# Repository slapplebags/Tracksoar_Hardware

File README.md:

View this project on [CADLAB.io](https://cadlab.io/project/1187). 

# Tracksoar_Hardware

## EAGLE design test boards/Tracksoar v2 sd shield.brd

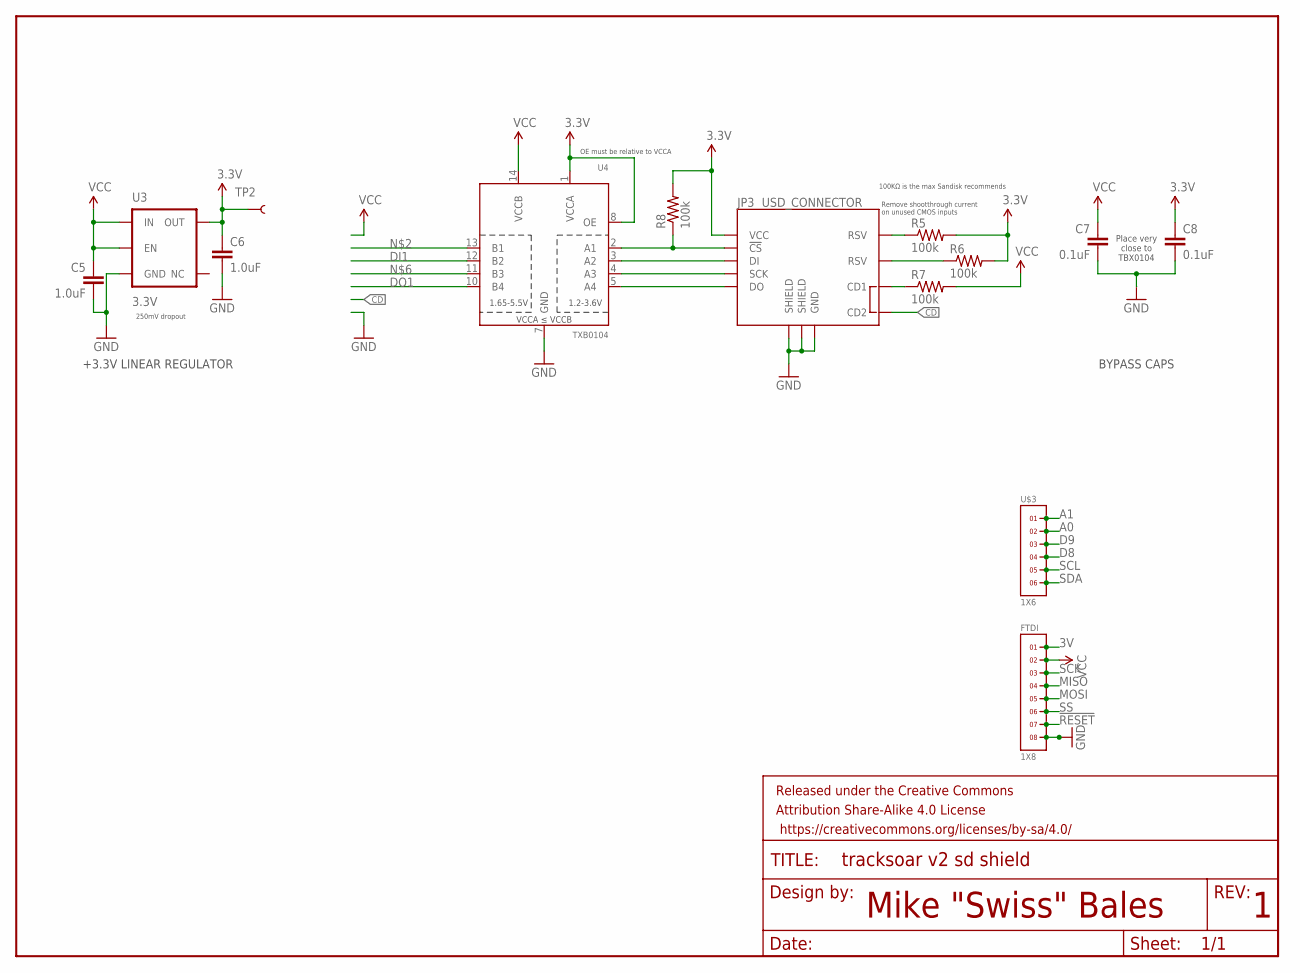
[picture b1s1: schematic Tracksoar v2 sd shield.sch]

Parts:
C5, C6: 1.0uF; 0603-CAP
C7, C8: 0.1uF; 0603-CAP
FRAME1: FRAME-LETTER; CREATIVE_COMMONS
FTDI: 1X8
JP3: USD_CONNECTOR; MICRO-SD-SOCKET-PP
R5, R6, R7, R8: 100k; 0603-RES
TP2: TEST-POINT3; PAD.03X.03
U3: 3.3V; SOT23-5
U4: TXB0104; SO14
U$3: 1X6

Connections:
3V: FTDI.1
3V3: C6.1, C8.1, JP3.VCC, R5.2, R6.2, R8.2, TP2.P$1, U3.5 (OUT), U4.1 (VCCA), U4.8 (OE)
!CS_3V1: JP3.CS (!CS), R8.1, U4.2 (A1)
!RESET: FTDI.7
A0: U$3.2
A1: U$3.1
CD: JP3.CD2
CDSDSD1: JP3.CD1, R7.1
D8: U$3.4
D9: U$3.3
DI1: U4.12 (B2)
DI_3V1: JP3.DI, U4.3 (A2)
DO1: U4.10 (B4)
DO_3V1: JP3.DO, U4.5 (A4)
GND: C5.2, C6.2, C7.2, C8.2, FTDI.8, JP3.GND, JP3.GND1 (SHIELD), JP3.GND3 (SHIELD), U3.2 (GND), U4.7 (GND)
MISO: FTDI.4
MOSI: FTDI.5
RSV@3: JP3.RSV1 (RSV), R5.1
RSV@4: JP3.RSV2 (RSV), R6.1
SCK: FTDI.3
SCK_3V1: JP3.SCLK (SCK), U4.4 (A3)
SCL: U$3.5
SDA: U$3.6
SS: FTDI.6
VCC: FTDI.2
VDD_IO: C5.1, C7.1, R7.2, U3.1 (IN), U3.3 (EN), U4.14 (VCCB)

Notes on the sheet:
Mike "Swiss" Bales
Remove shootthrough current on unused CMOS inputs
Place very close to TBX0104
OE must be relative to VCCA
+3.3V LINEAR REGULATOR
BYPASS CAPS
100KΩ is the max Sandisk recommends
250mV dropout

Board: 4 copper layers, 15 parts (13 on the bottom side), 10 nets, no tracks yet.

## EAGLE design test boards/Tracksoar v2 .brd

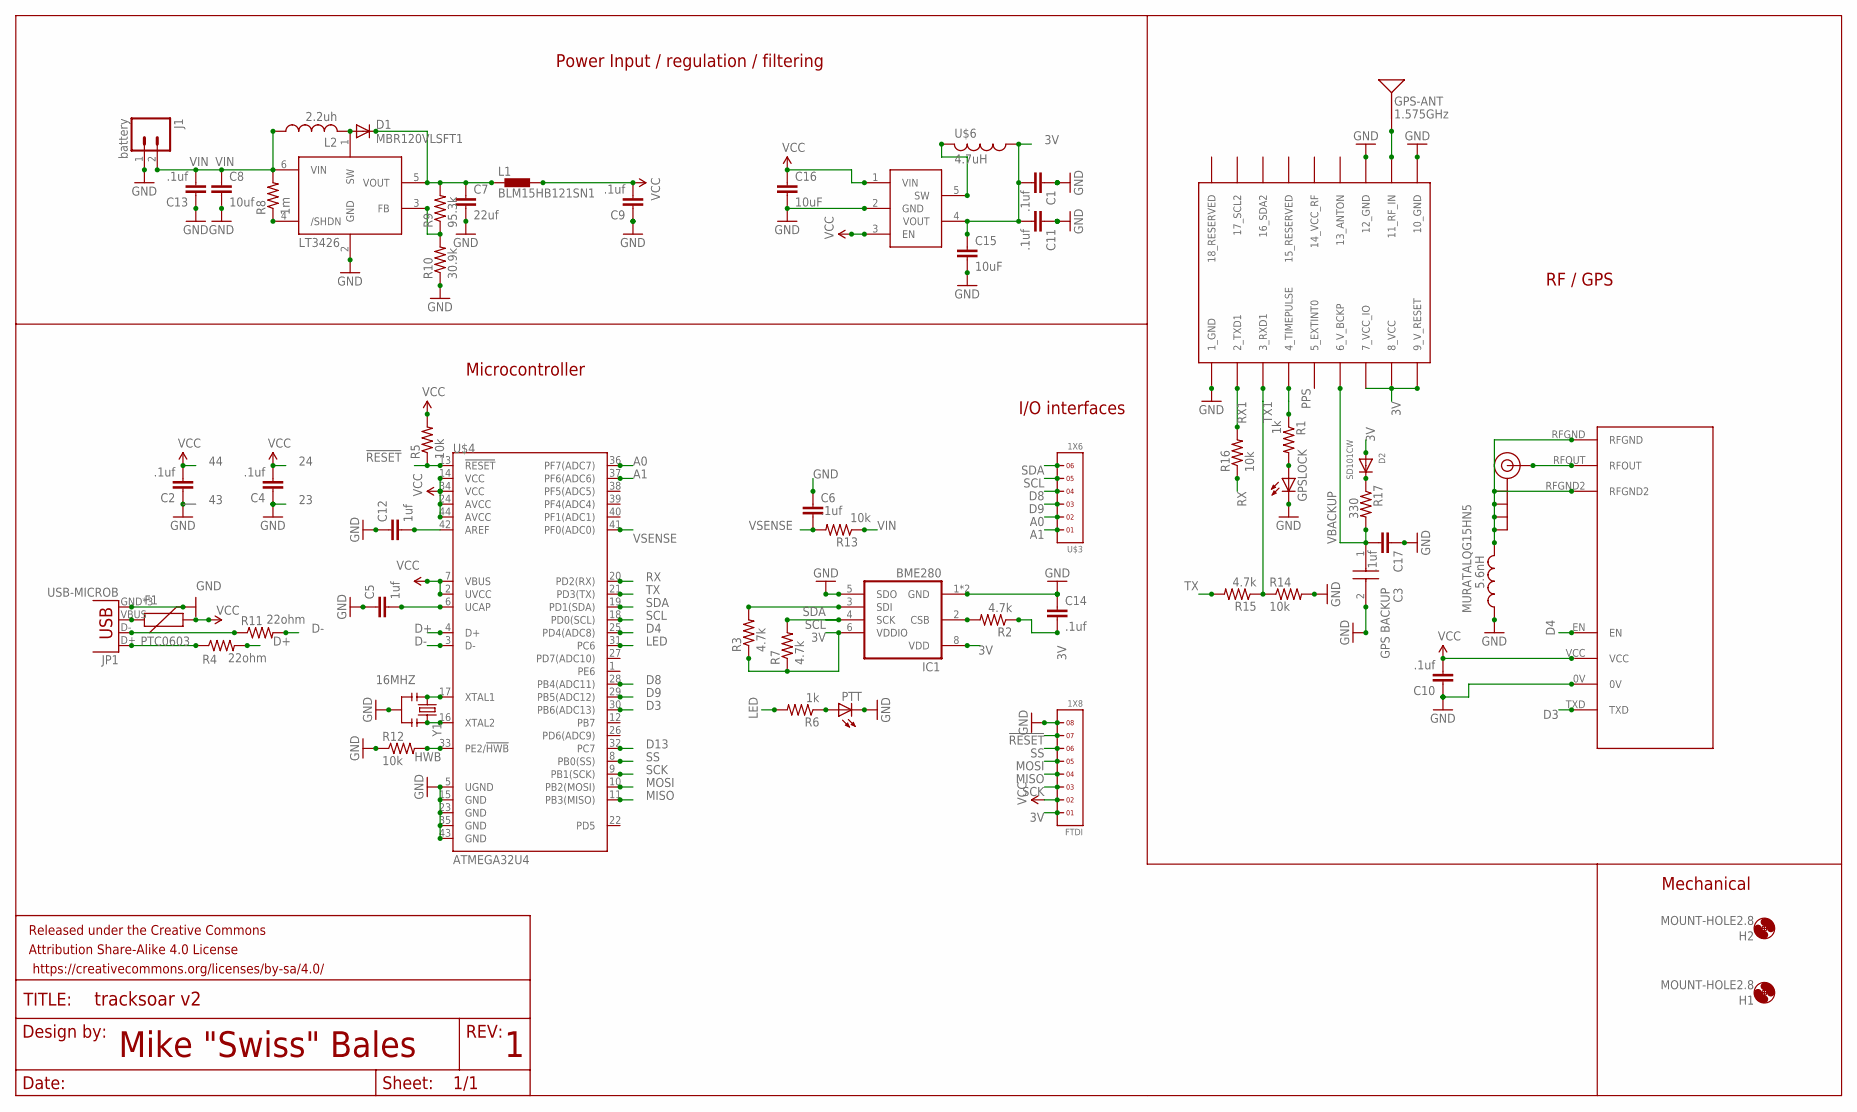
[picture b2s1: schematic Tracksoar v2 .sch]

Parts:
C1, C2, C4, C6, C9, C10, C11, C13, C14, C17: .1uf; 0402-CAP
C3: GPS BACKUP; DSK-3R3H204T614-H2L
C5, C12: 1uf; 0402-CAP
C7: 22uf; 0805
C8: 10uf; 0805
C15, C16: 10uF; 0603
D1: MBR120VLSFT1; SOD123
D2: SD101CW; SOD-123
F1: PTC0603; 0603
FRAME1: FRAME-LETTER; CREATIVE_COMMONS
FTDI: 1X8
GPS-ANT: 1.575GHz; ANT-GPS-2X7MM
GPSLOCK: LEDCHIP-LED0603; CHIP-LED0603
H1, H2: MOUNT-HOLE2.8; 2,8
IC1: BME280
J1: battery; JST-2-PTH
J$1: SMA_EDGE; SMA-EDGE
JP1: USB-MICROB
L1: BLM15HB121SN1; 0402
L2: 2.2uh; L1812
LT3426: LT3426; SOT23-6
MURATALQG15HN5: 5.6nH; RESC0402_N
PTT: LEDCHIP-LED0603; CHIP-LED0603
R1, R6: 1k; R0402
R2, R3, R7, R15: 4.7k; R0402
R4, R11: 22ohm; R0402
R5, R12, R13, R14, R16: 10k; R0402
R8: 1m; R0402
R9: 95.3k; R0402
R10: 30.9k; R0402
R17: 330; R0402
U$1: UBLOX_MAX
U$2: RADIOMETRIX-HX1
U$3: 1X6
U$4: ATMEGA32U4; QFN-44-NOPAD
U$5: PAM2305; DBV_R-PDSO-G5
U$6: 4.7uH; RESC0805_N
Y1: 16MHZ; RESONATOR-SMD

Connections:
3V: C1.2, C11.2, C14.2, C15.1, D2.A, FTDI.1, IC1.6 (VDDIO), IC1.8 (VDD), R2.1, R3.1, R7.1, U$1.7_VCC_IO, U$1.8_VCC, U$1.9_V_RESET, U$5.4 (VOUT), U$6.1
!RESET: FTDI.7, R5.1, U$4.13 (!RESET)
A0: U$3.2, U$4.36 (PF7(ADC7))
A1: U$3.1, U$4.37 (PF6(ADC6))
D3: U$2.TXD, U$4.30 (PB6(ADC13))
D4: U$2.EN, U$4.25 (PD4(ADC8))
D8: U$3.4, U$4.28 (PB4(ADC11))
D9: U$3.3, U$4.29 (PB5(ADC12))
D13: U$4.32 (PC7)
D+: R4.2, U$4.4 (D+)
D-: R11.2, U$4.3 (D-)
GND: C1.1, C2.1, C3.2 (-), C4.1, C5.1, C6.1, C7.2, C8.2, C9.1, C10.1, C11.1, C12.1, C13.1, C14.1, C15.2, C16.2, C17.1, FTDI.8, GPSLOCK.C, IC1.1 (GND), IC1.5 (SDO), IC1.7 (GND), J1.1, JP1.GND, JP1.MT1 (GND), JP1.MT2 (GND), LT3426.2 (GND), MURATALQG15HN5.1, PTT.C, R10.1, R12.1, R14.2, U$1.1_GND, U$1.10_GND, U$1.12_GND, U$2.0V, U$4.5 (UGND), U$4.15 (GND), U$4.23 (GND), U$4.35 (GND), U$4.43 (GND), U$5.2 (GND), Y1.2
HWB: R12.2, U$4.33 (PE2/!HWB)
LED: R6.2, U$4.31 (PC6)
MISO: FTDI.4, U$4.11 (PB3(MISO))
MOSI: FTDI.5, U$4.10 (PB2(MOSI))
unnamed: J$1.SIG (SIGNAL), U$2.RFOUT
unnamed: IC1.2 (CSB), R2.2
unnamed: GPSLOCK.A, R1.2
unnamed: GPS-ANT.1, U$1.11_RF_IN
unnamed: JP1.D-, R11.1
unnamed: JP1.D+, R4.1
unnamed: D1.A, L2.2, LT3426.1 (SW)
unnamed: LT3426.4 (/SHDN), R8.1
unnamed: LT3426.3 (FB), R9.1, R10.2
unnamed: F1.1, JP1.VBUS
unnamed: C12.2, U$4.42 (AREF)
unnamed: C7.1, D1.C, L1.1, LT3426.5 (VOUT), R9.2
unnamed: C5.2, U$4.6 (UCAP)
unnamed: U$5.5 (SW), U$6.2
unnamed: D2.C, R17.1
unnamed: PTT.A, R6.1
PPS: R1.1, U$1.4_TIMEPULSE
RFGND: J$1.GND@0 (GND), J$1.GND@1 (GND), J$1.GND@2 (GND), J$1.GND@3 (GND), MURATALQG15HN5.2, U$2.RFGND, U$2.RFGND2
RX: R16.1, U$4.20 (PD2(RX))
RX1: R16.2, U$1.2_TXD1
SCK: FTDI.3, U$4.9 (PB1(SCK))
SCL: IC1.4 (SCK), R7.2, U$3.5, U$4.18 (PD0(SCL))
SDA: IC1.3 (SDI), R3.2, U$3.6, U$4.19 (PD1(SDA))
SS: FTDI.6, U$4.8 (PB0(SS))
TX: R15.2, U$4.21 (PD3(TX))
TX1: R14.1, R15.1, U$1.3_RXD1
VBACKUP: C3.1 (+), C17.2, R17.2, U$1.6_V_BCKP
VCC: C2.2, C4.2, C9.2, C10.2, C16.1, F1.2, FTDI.2, L1.2, R5.2, U$2.VCC, U$4.2 (UVCC), U$4.7 (VBUS), U$4.14 (VCC), U$4.24 (AVCC), U$4.34 (VCC), U$4.44 (AVCC), U$5.1 (VIN), U$5.3 (EN)
VIN: C8.1, C13.2, J1.2, L2.1, LT3426.6 (VIN), R8.2, R13.1
VSENSE: C6.2, R13.2, U$4.41 (PF0(ADC0))
XTAL1: U$4.17 (XTAL1), Y1.1
XTAL2: U$4.16 (XTAL2), Y1.3

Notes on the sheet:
Mike "Swiss" Bales
Power Input / regulation / filtering
RF / GPS
Microcontroller
I/O interfaces
Mechanical

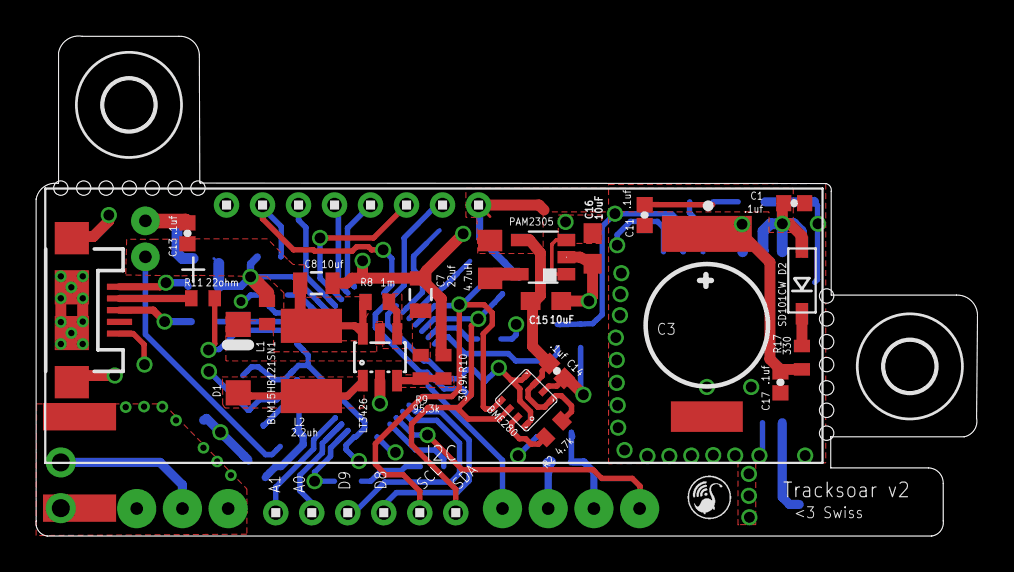
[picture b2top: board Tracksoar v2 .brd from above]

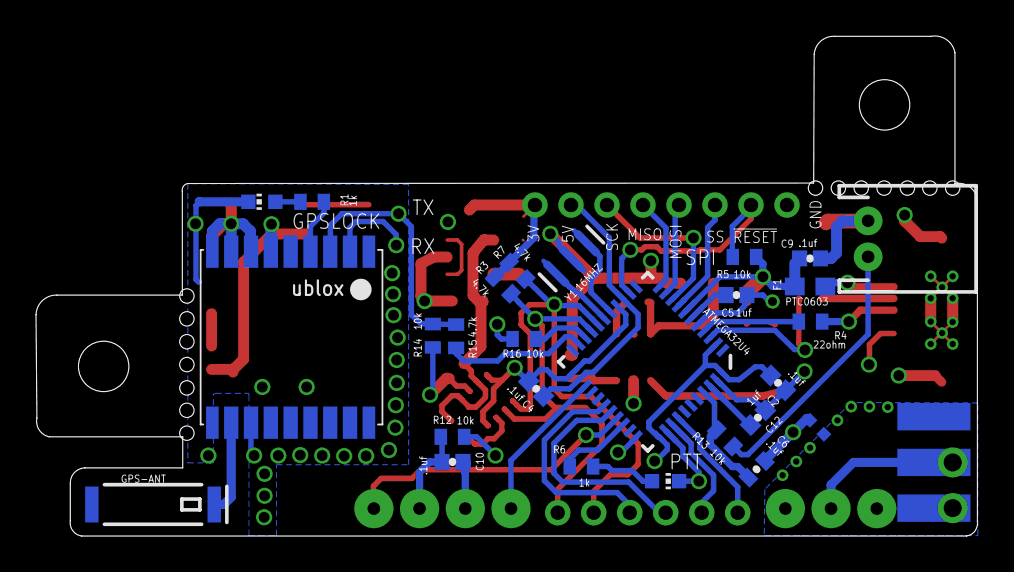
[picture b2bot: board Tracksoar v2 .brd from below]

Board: 4 copper layers, 52.3 x 27.8 mm, 59 parts (28 on the bottom side), 47 nets.

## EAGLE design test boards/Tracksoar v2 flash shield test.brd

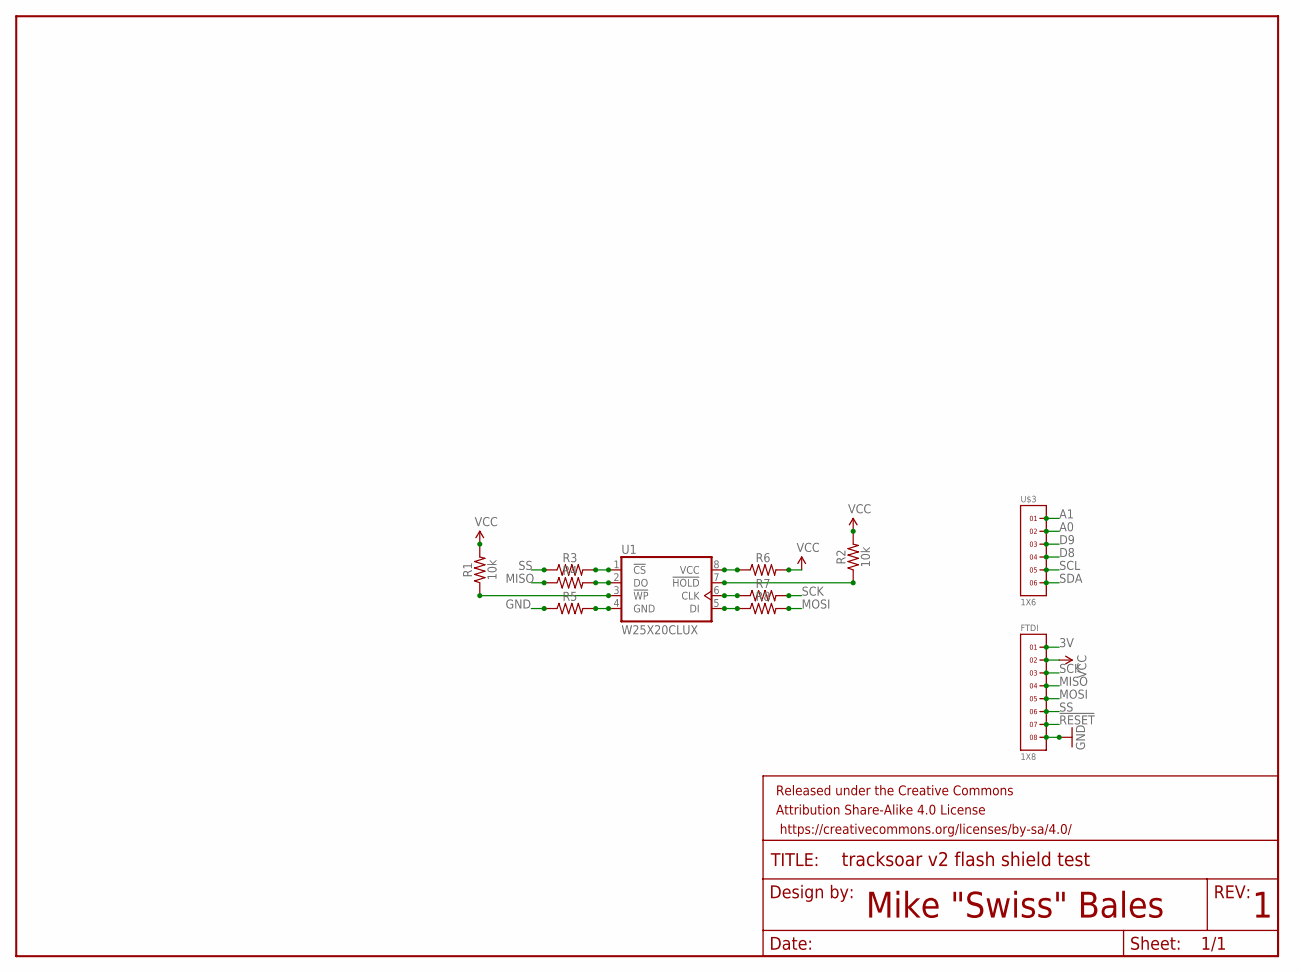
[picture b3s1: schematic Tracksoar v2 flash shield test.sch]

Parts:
FRAME1: FRAME-LETTER; CREATIVE_COMMONS
FTDI: 1X8
R1, R2: 10k; 0603
R3, R4, R5, R6, R7, R8: 0603
U1: W25X20CLUX; SON-8-50P-300W-200L-100H-40F-20EW-165EL
U$3: 1X6

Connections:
3V: FTDI.1
!RESET: FTDI.7
A0: U$3.2
A1: U$3.1
D8: U$3.4
D9: U$3.3
GND: FTDI.8, R5.1
MISO: FTDI.4, R4.1
MOSI: FTDI.5, R8.2
unnamed: R1.1, U1.3 (!WP!)
unnamed: R2.1, U1.7 (!HOLD!)
unnamed: R3.2, U1.1 (!CS!)
unnamed: R4.2, U1.2 (DO)
unnamed: R5.2, U1.4 (GND)
unnamed: R6.1, U1.8 (VCC)
unnamed: R7.1, U1.6 (CLK)
unnamed: R8.1, U1.5 (DI)
SCK: FTDI.3, R7.2
SCL: U$3.5
SDA: U$3.6
SS: FTDI.6, R3.1
VCC: FTDI.2, R1.2, R2.2, R6.2

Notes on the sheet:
Mike "Swiss" Bales

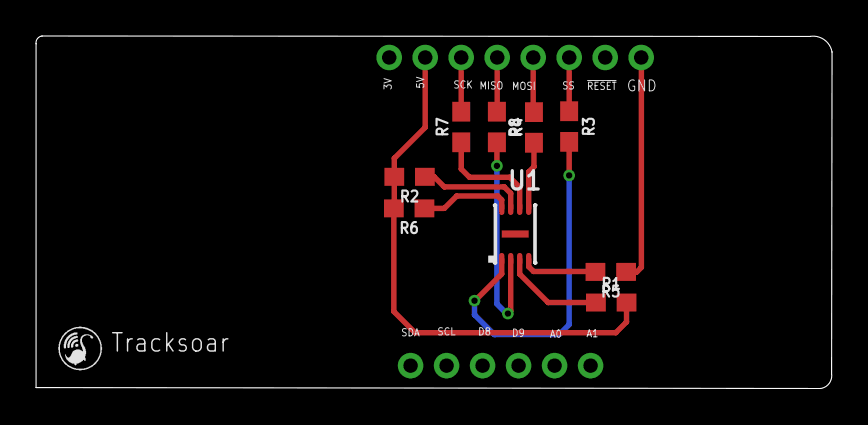
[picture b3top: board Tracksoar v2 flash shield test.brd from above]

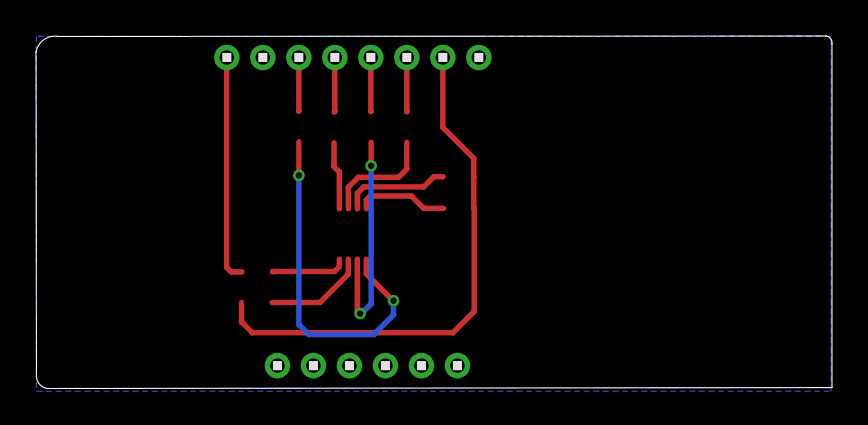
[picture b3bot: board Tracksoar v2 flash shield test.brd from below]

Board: 4 copper layers, 44.2 x 19.6 mm, 12 parts (2 on the bottom side), 14 nets.

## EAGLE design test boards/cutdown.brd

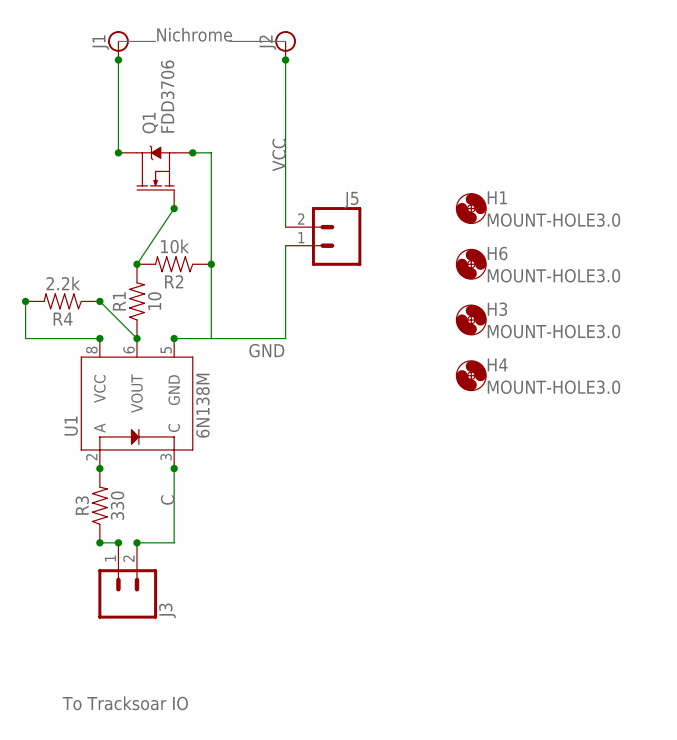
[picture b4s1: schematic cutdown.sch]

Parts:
H1, H3, H4, H6: MOUNT-HOLE3.0; 3,0
J1, J2: BANANA_CONN
J3, J5: CONN_02PTH3; 1X02_LONGPADS
Q1: FDD3706; DPAK
R1: 10; 0603
R2: 10k; 0603
R3: 330; 0603
R4: 2.2k; 0603
U1: 6N138M; 8-SMD

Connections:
A: J3.1, R3.1
C: J3.2, U1.3 (C)
GND: J5.1, Q1.3 (S), R2.1, U1.5 (GND)
unnamed: J1.P$1, Q1.4 (D)
unnamed: Q1.1 (G), R1.2, R2.2
unnamed: R1.1, R4.1, U1.6 (VOUT)
unnamed: R3.2, U1.2 (A)
unnamed: R4.2, U1.8 (VCC)
VCC: J2.P$1, J5.2

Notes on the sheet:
Nichrome
To Tracksoar IO

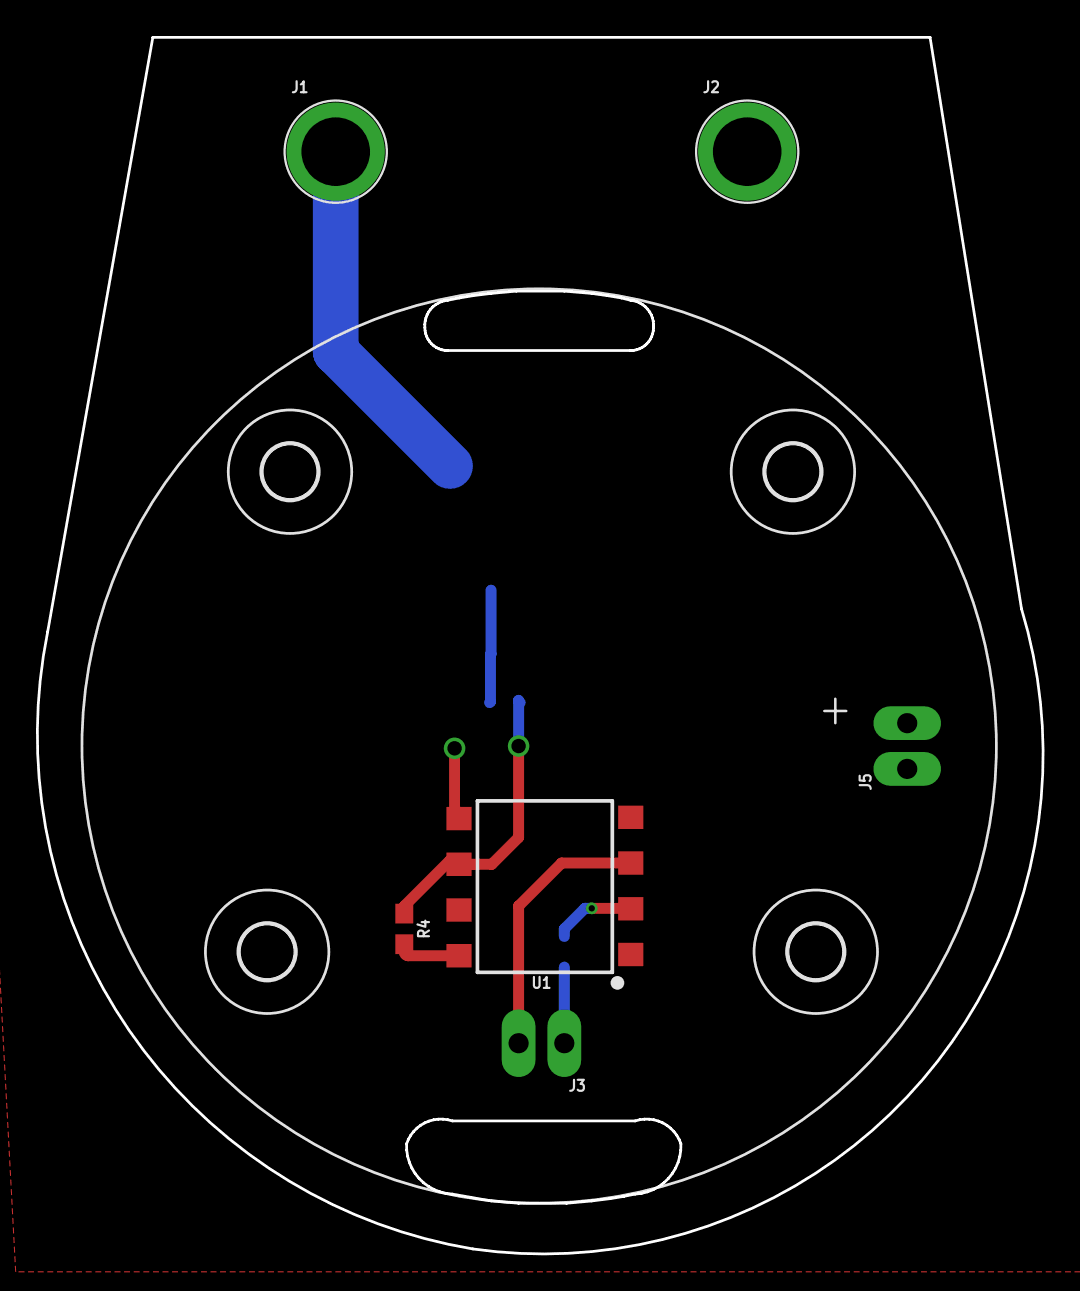
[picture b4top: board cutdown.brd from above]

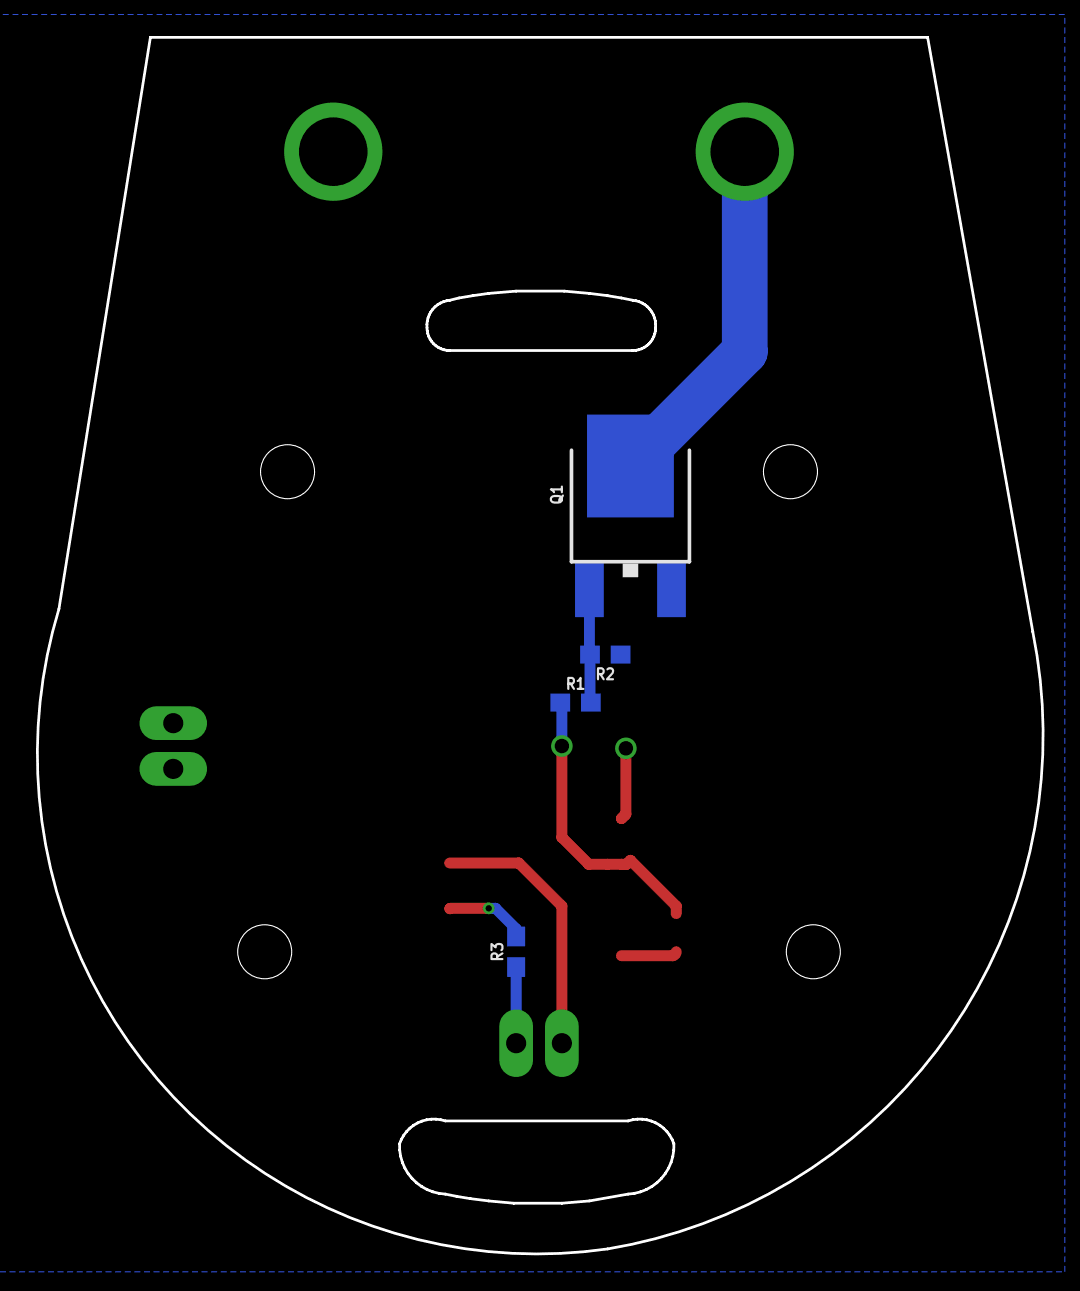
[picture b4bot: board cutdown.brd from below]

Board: 2 copper layers, 55.9 x 67.6 mm, 14 parts (4 on the bottom side), 9 nets.

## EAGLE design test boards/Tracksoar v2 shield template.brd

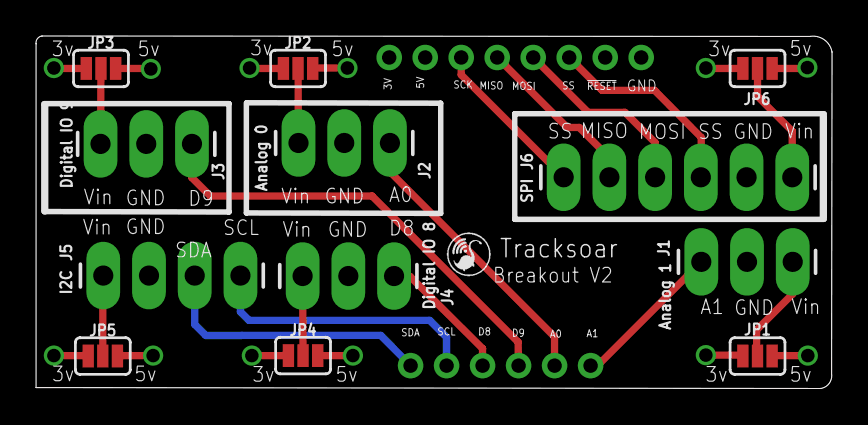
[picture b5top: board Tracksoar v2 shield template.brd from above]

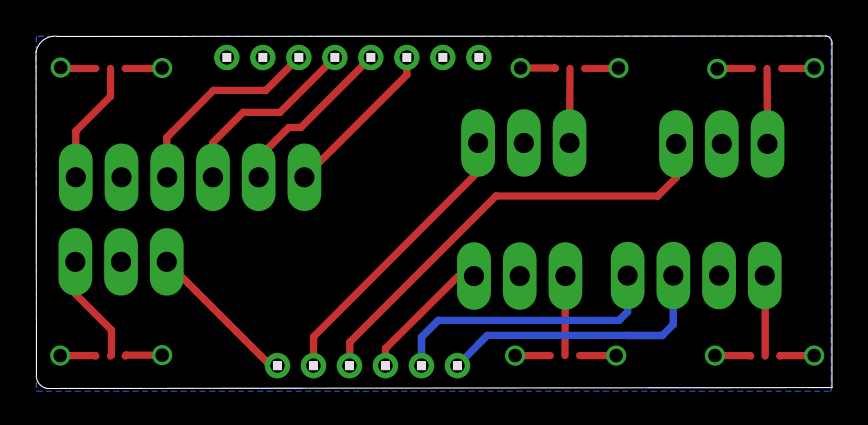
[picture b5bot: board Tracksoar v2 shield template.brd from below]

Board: 4 copper layers, 44.2 x 19.6 mm, 15 parts (2 on the bottom side), 19 nets.

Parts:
FRAME1: FRAME-LETTER; CREATIVE_COMMONS
FTDI: 1X8
J1: Analog 1; 1X03_LONGPADS
J2: Analog 0; 1X03_LONGPADS
J3: Digital IO 9; 1X03_LONGPADS
J4: Digital IO 8; 1X03_LONGPADS
J5: I2C; 1X04_LONGPADS
J6: SPI; 1X06_LONGPADS
JP1, JP2, JP3, JP4, JP5, JP6: JUMPER-SMT_3_1-NC_PASTE_SILK; SMT-JUMPER_3_1-NC_PASTE_SILK
U$3: 1X6

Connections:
3V: FTDI.1, JP1.1, JP2.1, JP3.1, JP4.1, JP5.1, JP6.1
A0: J2.3, U$3.2
A1: J1.3, U$3.1
D8: J4.3, U$3.4
D9: J3.3, U$3.3
GND: FTDI.8, J1.2, J2.2, J3.2, J4.2, J5.2, J6.2
MISO: FTDI.4, J6.5
MOSI: FTDI.5, J6.4
unnamed: J1.1, JP1.2
unnamed: J2.1, JP2.2
unnamed: J3.1, JP3.2
unnamed: J4.1, JP4.2
unnamed: J5.1, JP5.2
unnamed: J6.1, JP6.2
SCK: FTDI.3, J6.6
SCL: J5.4, U$3.5
SDA: J5.3, U$3.6
SS: FTDI.6, J6.3
VCC: FTDI.2, JP1.3, JP2.3, JP3.3, JP4.3, JP5.3, JP6.3

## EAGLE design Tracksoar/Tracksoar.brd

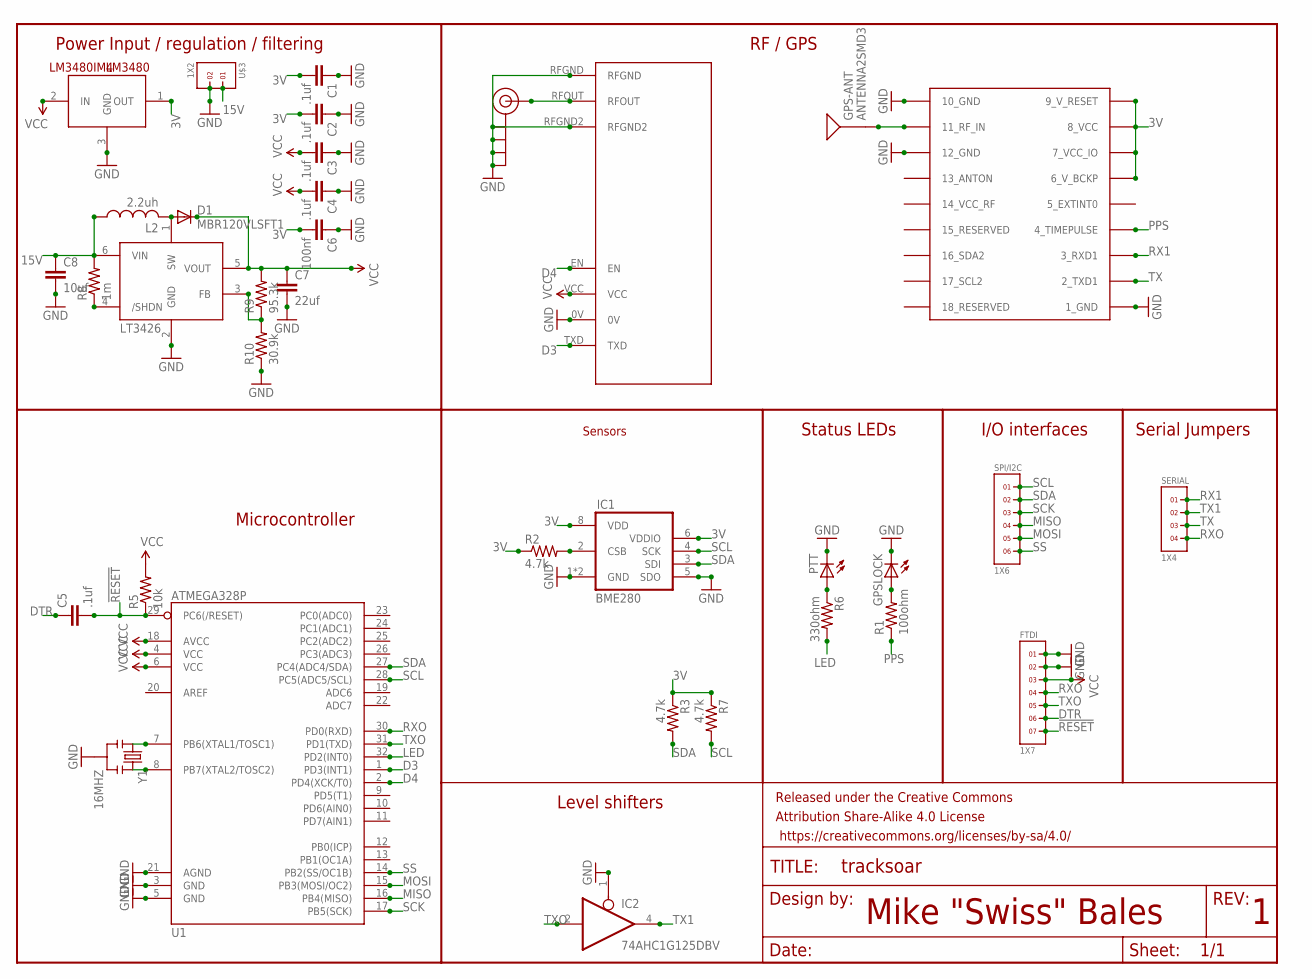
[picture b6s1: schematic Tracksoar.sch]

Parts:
C1, C2, C3, C4, C5: .1uf; 0805
C6: 100nf; 0805
C7: 22uf; 0805
C8: 10uf; 0805
D1: MBR120VLSFT1; SOD123
FRAME1: FRAME-LETTER; CREATIVE_COMMONS
FTDI: 1X7
GPS-ANT: ANTENNA2SMD3; ANTENNA-CHIP4
GPSLOCK: LEDCHIP-LED0805; CHIP-LED0805
IC1: BME280
IC2: 74AHC1G125DBV; SOT23-5
J$1: SMA_EDGE; SMA-EDGE
L2: 2.2uh; L1812
LM3480: LM3480IM4; SOT23-3
LT3426: LT3426; SOT23-6
PTT: LEDCHIP-LED0805; CHIP-LED0805
R1: 100ohm; 0805
R2, R3, R7: 4.7k; 0805
R5: 10k; 0805
R6: 330ohm; 0805
R8: 1m; 0805
R9: 95.3k; 0805
R10: 30.9k; 0805
SERIAL: 1X4
SPI/I2C: 1X6
U1: ATMEGA328P; MLF32
U$1: UBLOX_MAX
U$2: RADIOMETRIX-HX1
U$3: 1X2
Y1: 16MHZ; RESONATOR-SMD

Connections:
3V: C1.2, C2.2, C6.2, IC1.6 (VDDIO), IC1.8 (VDD), LM3480.1 (OUT), R2.1, R3.1, R7.1, U$1.6_V_BCKP, U$1.7_VCC_IO, U$1.8_VCC, U$1.9_V_RESET
15V: C8.1, L2.1, LT3426.6 (VIN), R8.2, U$3.1
!RESET: C5.2, FTDI.7, R5.1, U1.29 (PC6(/RESET))
D3: U1.1 (PD3(INT1)), U$2.TXD
D4: U1.2 (PD4(XCK/T0)), U$2.EN
DTR: C5.1, FTDI.6
GND: C1.1, C2.1, C3.1, C4.1, C6.1, C7.2, C8.2, FTDI.1, FTDI.2, GPSLOCK.C, IC1.1 (GND), IC1.5 (SDO), IC1.7 (GND), IC2.1 (OE), IC2.3 (GND), J$1.GND@0 (GND), J$1.GND@1 (GND), J$1.GND@2 (GND), J$1.GND@3 (GND), LM3480.3 (GND), LT3426.2 (GND), PTT.C, R10.1, U1.3 (GND), U1.5 (GND), U1.21 (AGND), U$1.1_GND, U$1.10_GND, U$1.12_GND, U$2.0V, U$2.RFGND, U$2.RFGND2, U$3.2, Y1.2
LED: R6.2, U1.32 (PD2(INT0))
MISO: SPI/I2C.4, U1.16 (PB4(MISO))
MOSI: SPI/I2C.5, U1.15 (PB3(MOSI/OC2))
unnamed: J$1.SIG (SIGNAL), U$2.RFOUT
unnamed: IC1.2 (CSB), R2.2
unnamed: GPSLOCK.A, R1.2
unnamed: GPS-ANT.SIG, U$1.11_RF_IN
unnamed: D1.A, L2.2, LT3426.1 (SW)
unnamed: LT3426.4 (/SHDN), R8.1
unnamed: LT3426.3 (FB), R9.1, R10.2
unnamed: U1.8 (PB7(XTAL2/TOSC2)), Y1.3
unnamed: U1.7 (PB6(XTAL1/TOSC1)), Y1.1
unnamed: PTT.A, R6.1
PPS: R1.1, U$1.4_TIMEPULSE
RX1: SERIAL.1, U$1.3_RXD1
RXO: FTDI.4, SERIAL.4, U1.30 (PD0(RXD))
SCK: SPI/I2C.3, U1.17 (PB5(SCK))
SCL: IC1.4 (SCK), R7.2, SPI/I2C.1, U1.28 (PC5(ADC5/SCL))
SDA: IC1.3 (SDI), R3.2, SPI/I2C.2, U1.27 (PC4(ADC4/SDA))
SS: SPI/I2C.6, U1.14 (PB2(SS/OC1B))
TX: SERIAL.3, U$1.2_TXD1
TX1: IC2.4 (O), SERIAL.2
TXO: FTDI.5, IC2.2 (I), U1.31 (PD1(TXD))
VCC: C3.2, C4.2, C7.1, D1.C, FTDI.3, IC2.5 (VCC), LM3480.2 (IN), LT3426.5 (VOUT), R5.2, R9.2, U1.4 (VCC), U1.6 (VCC), U1.18 (AVCC), U$2.VCC

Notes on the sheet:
Mike "Swiss" Bales
Power Input / regulation / filtering
RF / GPS
Microcontroller
Level shifters
Status LEDs
I/O interfaces
Serial Jumpers
Sensors

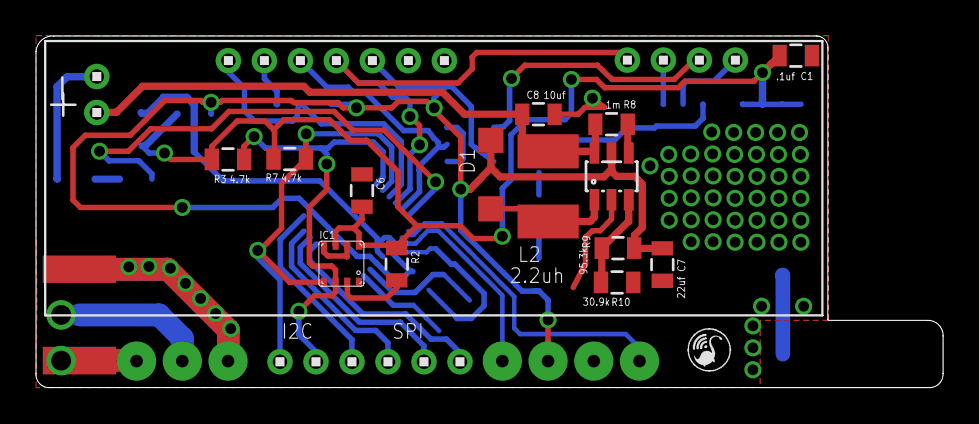
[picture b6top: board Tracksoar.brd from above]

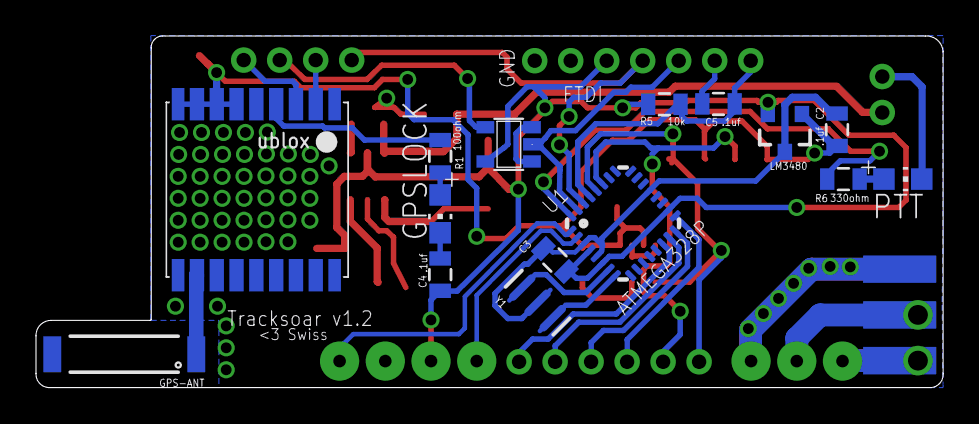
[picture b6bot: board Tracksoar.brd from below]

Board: 2 copper layers, 50.4 x 19.5 mm, 36 parts (16 on the bottom side), 31 nets.

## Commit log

2016-09-05 Added V1.1 board layout
2016-09-05 Added V1.2 board
2016-09-05 Added active gps branch
2016-09-05 Added back all archive info, this can be merged into master to keep changes or left here to store.
2017-04-27 Added Tracksoar Test Board
    This is the Tracksoar V2 Rev4 test board.
2017-04-29 tracksoar v2 rev 5
    converted to 4 layer board, covered via with solder mask, routed vcc
    and gnd on internal planes. Corrected AREF connection to ground via
    cap. Added analog pin connection to 15v to measure battery voltage.
    General routing cleanup.
2017-04-29 Updated Via Tenting
    now vias are untented
2017-04-29 Soldermasked Vias and minor layout fixes
    solder masked vias to resolve soldering issues. Removed separated
    ground around RF output. Updated silkscreen to read v1.2 and prevent
    clipping of the L2 designator and value. Removed unnecessary ground
    vias. Fixed floating ground on BME280 sensor.
2017-04-29 Updated Silkscreen
    Updated capacitor values and schematic symbols. Updated silkscreen to
    remove overlaps and standardized text size.
2017-04-29 labelled headers
    added silkscreen labels to headers
2017-04-29 Corrected battery connector placement
    Moved the battery connector to the bottom side of the board to avoid
    conflicts with the USB connector
2017-05-01 Tracksoar V1.3
    Created a new test board Tracksoar v1.3 to resolve potential issues
    with the boost converter interfering with GPS reception.
2017-05-01 Updated Silkscreen on Tracksoar V1.3
    Added individual pin designators, moved silkscreen items away from
    vias, standardized designator and value font size.
2017-05-24 BME280 Decoupling Cap
    Added a 100nf decoupling cap next to the bme280
2017-05-25 v2 BME280 decoupling cap
    added decoupling cap to bme280 of v2 board.
2017-06-04 Added Pull down to HWB pin
    added a 10k pull down resistor to HWB to resolve issues flashing the
    boot loader
2017-06-05 Swapped Serial1 RX and TX
    Fixed an issue sending / receiving serial between the atmega32u4 and
    ublox max m8q by swapping the rx and tx pins on the atmega32u4.
2017-06-05 moved bme280 decoupling cap
    moved the bme280 decoupling cap a bit for aesthetic reasons.
2017-06-07 Silkscreen cleanup and additional analog pin
    removed as many silkscreen keep out errors as possible. Added a
    breakout for analog pin A1 to the bottom header.
2017-06-07 Added Schematic PDFs
    Added schematic PDFs
2018-03-08 Moved BME280
    moved the bme 280 sensor away from the 3v regulator to help mitigate thermal issues.
2018-03-08 Removed Pours
    removed pours from under the lm3480 to limit heat reaching the bme280
2018-03-08 added thermal pads
    added thermal pads and vias below the lm3480 to prevent biasing the temp sensor
2018-03-10 updated thermal pads
    updated thermal pads
2018-03-18 removed ldo and level shifter
    replaced the 3v ldo with a switching regulator, replaced level shifter with resistor dividers.
2018-03-18 added pdfs
    added pdfs of schematic and board layout
2018-03-23 updated rf paths
    seperated RF GND from GND and coupled via an inductor. Implemented path cleanups. Made all RF impedence matched.
2018-03-23 moved gpio header
    moved the gpioheader to better center it
2018-04-21 added buck regulator
    swapped the linear regulator for a buck converter.
2018-04-21 fixed 3v reg
    the 3v reg wiring was corrected and output cap moved closer to the regulator.
2018-04-21 Added gps backup cap
    added gps backup capacitor. Corrected serial voltage divider resistor values. Removed ground vias below gps module.
2018-04-21 minor trace cleanup
    moved a few traces around for aesthetics.
2018-04-21 moved gnd via
    ground via for the backup cap was interferring with the GPS pads.
2018-04-21 added gnd vias
    added ground vias to shorten ground paths for the ltc3426, backup battery
2018-04-22 added a library
    added the ava library
2018-04-28 updated shield template
    updated shield template to be a breakout board for all IO into .1" headers
2018-04-28 fixed short on serial RX of tracksoar v2
    fixed a short on the serial rx line that shorted it to ground due to a via. Updated silkscreen on the breakout board and named headers
2018-04-28 Updated breakout silkscreen
    cleaned up the breakout silkscreen
2018-04-28 fixed the v2 shield template
    renamed the breakout board and re-added the template.
2018-05-04 Fixed airwire issue
    Fixed an issue with the v2 board that resulted from upgrading eagle to v9. It caused lots of very short airwires.
2018-05-06 silkscreen updates
    minor silkscreen fixes
2018-05-06 updated breakout board silkscreen
    SCK pins was mis-labelled as SS
2018-05-27 Schematic cleanup
    first pass at making the schematic more readable. Moved components to be more in line with the board layout.
2018-05-28 added breakout mount holes
    added 2.8mm mounting holes with mouse bites for easy removal.
2018-06-09 minor silkscreen cleanup
    moved GPIO pin names down to clear connector
2018-06-09 more silkscreen tweaks
    made header labels larger added a1 label
2018-06-09 moved a1 label
    moved a1 label
2018-06-17 added cutdown boards
    added cutdown test boards
2018-06-17 updated board outline
    updated board outline to makek the bottom cutout complete.
2018-06-17 silkscreen cleanup
    moved silkscreen tvalues and bvalues to tnames and bnames so they show up correctly in macrofab / oshpark.
2018-06-20 Backlink to CADLAB.io has been added.
2018-06-29 added active gps board
    added a v2 version with active gps antenna
2018-07-14 Added boards
    Added boards for a cutdown circuit, spi flash storage and spi flash breakout board and a shield template.
2018-08-05 Schematic cleanup
    placed decoupling caps where they are located on the board. Placed items in groups and did my best to place nets near their origins. Also generally group items where they are located on the board.
2018-08-06 Added mechanical drawing
    added mechanical drawing with dimensions in mm
2019-02-22 Create License
2019-05-08 Updated U$7
    updated u$7 on brd and sch file to include value and part number

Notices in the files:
parts and their libraries:
SparkFun-PowerIC: Licensing: Creative Commons ShareAlike 4.0 International - https://creativecommons.org/licenses/by-sa/4.0
SparkFun-Aesthetics: Released under the Creative Commons Attribution Share-Alike 4.0 License
SparkFun-Aesthetics: https://creativecommons.org/licenses/by-sa/4.0
